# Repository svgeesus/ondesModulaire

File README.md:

ondesModulaire
==============

Eurorack analog synth implementation of ondes Martenot. This uses a
mixture of commercial and DIY modules. The controllers and the speakers
are all DIY. See [the patch](Patch.md).

This repository documents the DIY modules that I am making specific to
this project (as opposed to kits or designs made by others).

- [Precision rectifier](precision%20rectifier/readme.md)
- [Dual Comparator](dual%20comparator/)
- [ondesMix](wavemix/)
- [Offsets](offsets/)

It is also documenting the controllers I am making, and the speakers.

The keyboard controller was started, was partly working, and was then
abandoned as the keybed was too heavy for the keyboard shake vibrato function.
The keys were also regular sized rather than the smaller OM style.
Documentation at http://nantonos.github.io/ondesModulaire/keyboard/docs/

Lastly, this repository houses resources (screenshots, recordings, notes)
related to ongoing experiments to find the best emulation.

[Planned state of the modules](http://www.modulargrid.net/e/racks/view/30175) is available on Modular Grid and is updated
as experiments proceed.

The [actual current state](http://www.modulargrid.net/e/racks/view/61770) is also available and is updated as modules are purchased, built, or designed and built,
respectively.

A [discussion thread on Muffs forum](http://www.muffwiggler.com/forum/viewtopic.php?p=1261346) is the main place where this and related
projects are discussed

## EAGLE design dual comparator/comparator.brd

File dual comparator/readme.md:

# Dual Comparator

## Introduction

This 6HP dual module is a pair of simple comparator circuits, which turns triangle waves into a pulse waves with variable mark/space ratio. It takes two audio inputs and two control voltages, compares them, and outputs the result. If a CV is not patched, a variable voltage is used (derived from a voltage reference and a pot).

If the input waveform is a triangle wave, the output is a pulse wave with a variable mark-space ratio controlled by the CV.

I needed this because the Ondes Martenot has _two_ pulse waveforms: Gambe and Nasillard.
Gambe is roughly a pulse wave with 45% mark/space. (Petit gambe is a lowpass-filtered version of Gambe).
Nasillard is another pulse, but with around 5% mark/space.

## Features

- two audio ins (in2 normalized to in1)
- two PW cv ins (normalized to 5V)
- two pulse outputs
- two pots, for attenuverters

## Implementation

Choice of op-amp to use as comparator informed by [AN-849 Using Op Amps as Comparators](./AN-849.pdf) and in particular, transition time, overload recovery time and absence of phase reversal. A small amount of positive feedback provides some hysteresis to give clean switching even if the input signal has noise around the switching threshold.

- two trimmers, to null attenuverter
- low cost REF195 5V ref (direct to norm pots)
- two audio input buffers (2 audio) TL074
- two CV attenuverters (other half of 074)
- LT1213 dual op-amp as comparator
- 10k/15k resistive divider converts +/- 12V output to+/- 5V output. Volt swing and slew rate of comparator is reduced by current draw.
- two output buffers (TL072) with 47R output impedance.
- small pcb with just 2 pots. 6 jacks wired to pcb.

[Schematic (PDF)](schematic.pdf)

 ([PDF](board.pdf))

]

[Bill of Materials](dual_comparator_BOM.md)

Front panel [FPD](./dual_comparator.fpd)

## Special Bonus Feature

This module was designed to sit next to an Intellijel Dixie 2 oscillator, providing an additional two pulse waveforms. The Dixie 2 has coarse and fine tune pots, and also on the PCB a three-pin connector for an optional, third, ultrafine tune. There was spare space on this module so I added a handy ultra-fine-tune pot. There are no jacks for this, use a 3-pin jumper cable to go from the internal 3-pin connector
to the 3-pin ultrafine connector on the Dixie.

This is utterly unrelated to the comparator functionality.

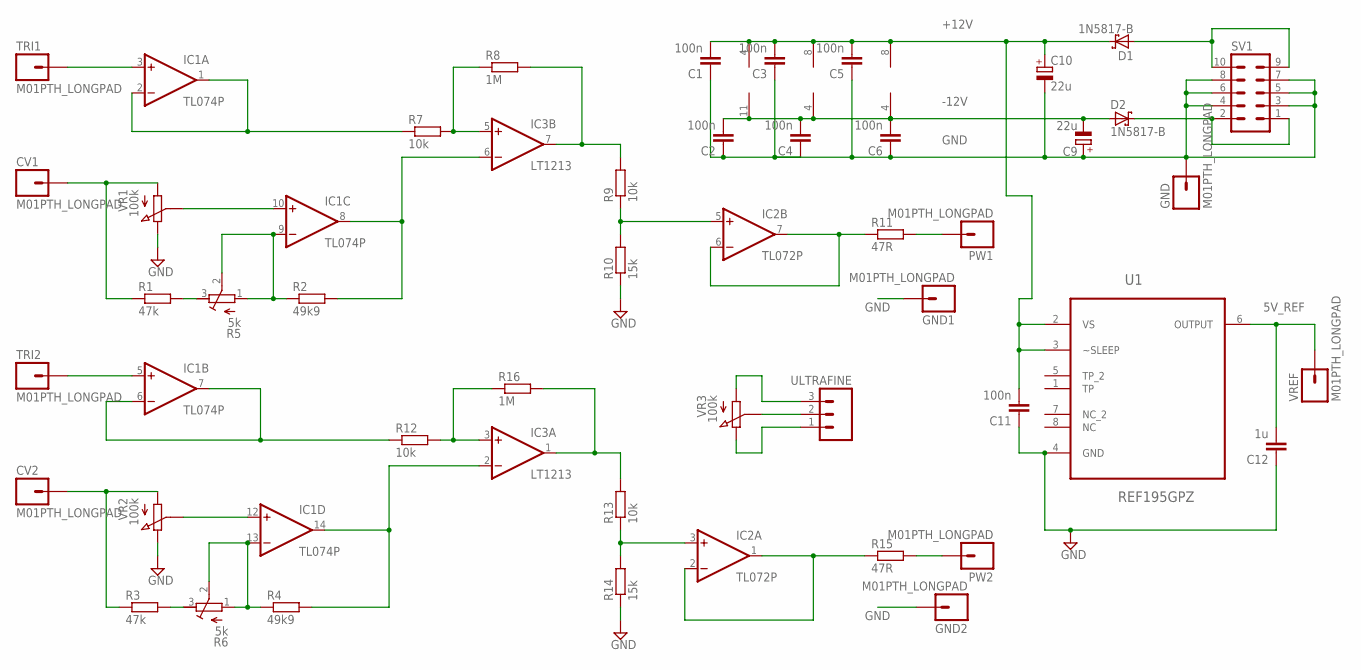
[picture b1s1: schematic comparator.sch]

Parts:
C1, C2, C3, C4, C5, C6, C11: 100n; C025-025X050
C9, C10: 22u; E2,5-5
C12: 1u; C050-025X075
CV1, CV2: M01PTH_LONGPAD; 1X01_LONGPAD
D1, D2: 1N5817-B; DO41-7.6
GND, GND1, GND2: M01PTH_LONGPAD; 1X01_LONGPAD
IC1: TL074P; DIL14
IC2: TL072P; DIL08
IC3: LT1213; DIL08
PW1, PW2: M01PTH_LONGPAD; 1X01_LONGPAD
R1, R3: 47k; 02.5-06.8/10
R2, R4: 49k9; 02.5-06.8/10
R5, R6: 5k; RTRIM3296W
R7, R9, R12, R13: 10k; 02.5-06.8/10
R8, R16: 1M; 02.5-06.8/10
R10, R14: 15k; 02.5-06.8/10
R11, R15: 47R; 02.5-06.8/10
SV1: MA05-2
TRI1, TRI2: M01PTH_LONGPAD; 1X01_LONGPAD
U1: REF195GPZ; DIP254P762X533-8
ULTRAFINE: M03LOCK; 1X03_LOCK
VR1, VR2, VR3: 100k; BI_9MM_SIDE
VREF: M01PTH_LONGPAD; 1X01_LONGPAD

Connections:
5V_REF: C12.2, U1.6 (OUTPUT), VREF.1
+12V: C1.2, C3.2, C5.2, C10.+, C11.2, D1.C, IC1.4 (V+), IC2.8 (V+), IC3.8 (V+), U1.2 (VS), U1.3 (~SLEEP)
-12V: C2.2, C4.2, C6.2, C9.-, D2.A, IC1.11 (V-), IC2.4 (V-), IC3.4 (V-)
GND: C1.1, C2.1, C3.1, C4.1, C5.1, C6.1, C9.+, C10.-, C11.1, C12.1, GND.1, GND1.1, GND2.1, R10.P$1 (1), R14.P$1 (1), SV1.3, SV1.4, SV1.5, SV1.6, SV1.7, SV1.8, U1.4 (GND), VR1.TOP, VR2.TOP
unnamed: IC1.3 (+IN), TRI1.1
unnamed: IC1.1 (OUT), IC1.2 (-IN), R7.P$1 (1)
unnamed: IC3.5 (+IN), R7.P$2 (2), R8.P$1 (1)
unnamed: PW1.1, R11.P$2 (2)
unnamed: IC1.10 (+IN), VR1.WIPER
unnamed: R3.P$2 (2), R6.3 (A)
unnamed: R1.P$2 (2), R5.3 (A)
unnamed: IC1.9 (-IN), R2.P$1 (1), R5.1 (E), R5.2 (S)
unnamed: IC1.8 (OUT), IC3.6 (-IN), R2.P$2 (2)
unnamed: IC3.7 (OUT), R8.P$2 (2), R9.P$2 (2)
unnamed: IC2.5 (+IN), R9.P$1 (1), R10.P$2 (2)
unnamed: IC2.6 (-IN), IC2.7 (OUT), R11.P$1 (1)
unnamed: IC3.3 (+IN), R12.P$2 (2), R16.P$1 (1)
unnamed: IC1.5 (+IN), TRI2.1
unnamed: IC1.6 (-IN), IC1.7 (OUT), R12.P$1 (1)
unnamed: IC1.12 (+IN), VR2.WIPER
unnamed: IC1.13 (-IN), R4.P$1 (1), R6.1 (E), R6.2 (S)
unnamed: IC1.14 (OUT), IC3.2 (-IN), R4.P$2 (2)
unnamed: IC3.1 (OUT), R13.P$2 (2), R16.P$2 (2)
unnamed: IC2.3 (+IN), R13.P$1 (1), R14.P$2 (2)
unnamed: IC2.1 (OUT), IC2.2 (-IN), R15.P$1 (1)
unnamed: PW2.1, R15.P$2 (2)
unnamed: ULTRAFINE.3, VR3.BOTTOM
unnamed: ULTRAFINE.1, VR3.TOP
unnamed: D1.A, SV1.9, SV1.10
unnamed: ULTRAFINE.2, VR3.WIPER
unnamed: D2.C, SV1.1, SV1.2
PW_CV1: CV1.1, R1.P$1 (1), VR1.BOTTOM
PW_CV2: CV2.1, R3.P$1 (1), VR2.BOTTOM

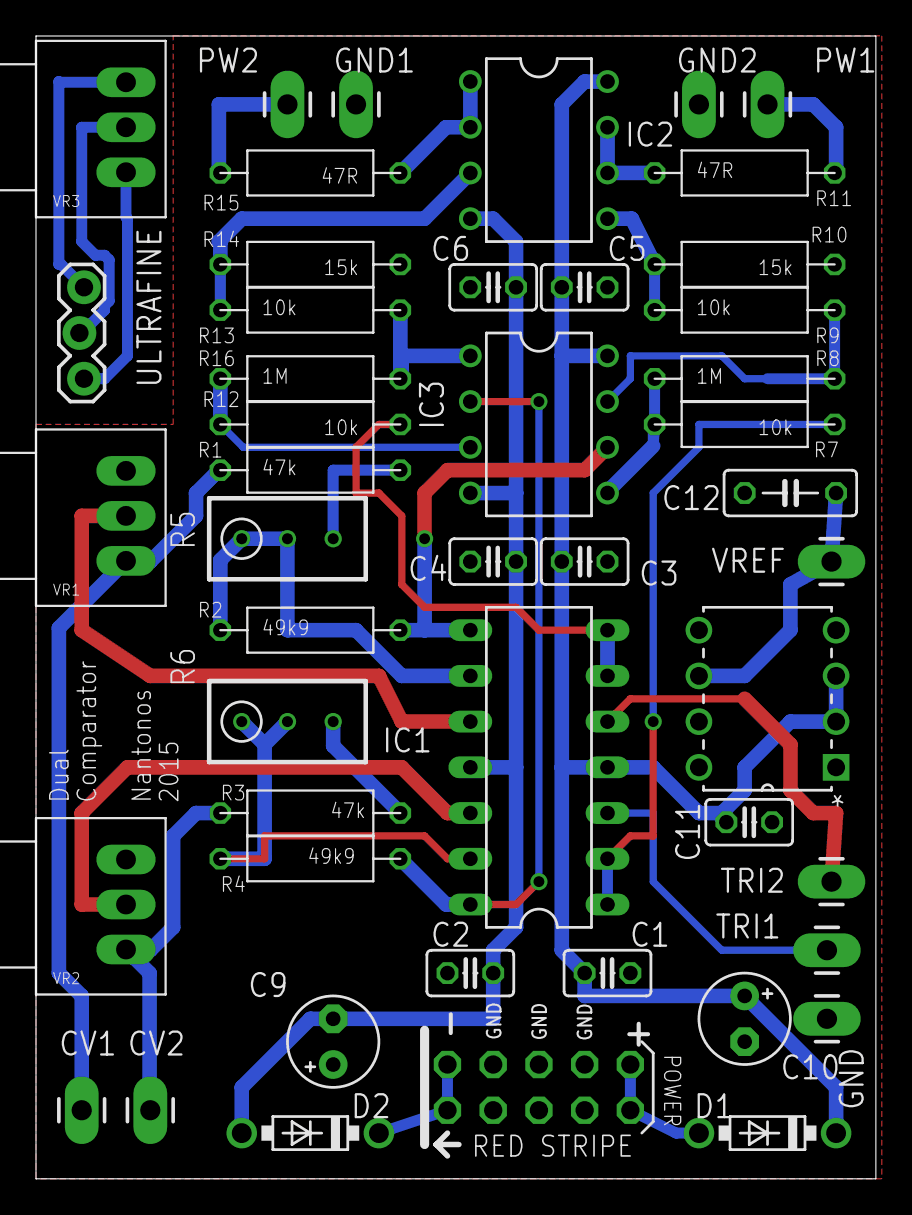
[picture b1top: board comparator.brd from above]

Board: 2 copper layers, 46.7 x 63.5 mm, 47 parts (0 on the bottom side), 33 nets.

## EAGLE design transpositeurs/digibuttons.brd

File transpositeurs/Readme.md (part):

# Digital implementation of transpositeurs (pitch shift buttons)

Transpositeurs are a set of six buttons,
in the tiroir of an ondes Martenot,
placed to the right of the _touche d'intensité_,
which produce small shifts in pitch.
They may be pressed in combination to generate larger shifts.
Effectively, a quantized pitchbend.

|  button   |   tones  |  semitones   | millivolts (semitones /12)    | interval     |
|--:        |--:       |--:           |--:                            |--:           |
| 1         | -1/4     | -0.5         |   -41.6666666666666667        | quarter-down |
| 2         | +1/4     | +0.5         |    41.6666666666666667        | quarter-up   |
| 3         | +1/2     | +1           |    83.3333333333333333        | semitone     |
| 4         | +1       | +2           |  166.666666666666667          | tone         |
| 5         | +2       | +4           |  333.333333333333333          | third        |
| 6         | +3 1/2   | +7           |  583.333333333333333          | fifth        |
| 2to6      |          | 14.5         | 1208.33333333333              |              |

Total swing 1,208.33333333333 - -41.6666666666667 = 1.250000V

My initial design attempts were purely analog. However,
analog buttons circuit is basically a DAC, so try designing as a DAC.

Since this is MCU based
and it only adds a couple of resistors and a connector,
an optional MIDI out is provided.

## Component selection

### MCU

A Teensy LC is ample for this simple circuit.

Make as an SPI board with 5V input (for vref, needs 1mA) and Euro ±12V (for op-amps).
Power DAC with 3V3 from Teensy? Or add on-board regulator for 3V3?
DAC needs 270(typ) 550(max) μA so power from Teensy 3V3 seems totally fine.

Teensy SPI for DAC on 10 (cs), 11 (Dout MOSI) 13 (SCLK)
free pins - maybe LEDs for buttons?

buttons not matrixed, hardware debounce, trigger interrupts.
transp. buttons need 6 inputs: 4,5,6,7,8,9

* try with bounce lib rather than hardware debounce.

breadboard debounce circuit, test debounced switch to interrupt ISR.
breadboard analog post-DAC circuit using Teensy LC pin14 DAC just for testing.

Could also have MIDI out on pin 1 TX1. Just send pitchbend.

### DAC

Total swing = 29 demi-semitones. Use DAC with total swing of n*32 so each
demisemitone is n integral steps, and avoid dac codes at the ends to
eliminate zero offset and max offset errors.

Aim is better than 1 cent accuracy = 1/50n so if n > 2^6 = 1/64n, for 1 lsb INL

Thus only needs a 12bit DAC (with very good <1.0 INL and DNL, n = 2^7 = 128) or
14bit with <4 INL, DNL, n = 2^9 = 512
16bit with <16INL, DNL

**LTC1658CS8** 14bit SPI SOIC-8 [got, ordered 13 Sep 2014]
SOIC-8, 3V3 or 5V operation
DNL ±1.0 LSB max, DNL graph shows ±0.2 LSB typ
INL ±8.0 LSB max (more than 0.1V from rails), but INL graph shows typ +1, -2LSB
DNL, INL assume Vref < Vcc -0.1V so use 3V ref and 3V3 rail.
zero error 4mV over temperature -40 to +85°C = DAC count 21.8 so avoid counts 0 to 22
offset error ±4.0 mV max over temperature -40 to +85°C so avoid counts 16,361 to 16,383
Offset Error Temperature Coefficient ±5 μV/°C
Gain error ±20 LSB
Gain Error Drift ±2.5 ppm/°C
Vref input resistance 30k min, so current = 100μA.
$6.05 from Linear, singly, min order 2; have both MSOP and DIP8
$10.27 from Mouser, moq 1

1LSB = 3 ÷ 2^14 = 183μV at DAC out, 1 cent is 833μV so 4.5LSB per cent.
but less than this as the DAC output is scaled down to total swing.

### Vref

DAC needs external vref, preferably a bit lower than Vcc so 3.0V would be good.
AD780 or, better and cheaper, MAX6126-3

**AD780BNZ**  1mv initial accuracy 3ppm/°C PDIP [got]
needs 1μF from VCC to GND
[ to lower noise, add 100nF from pin3 to GND and 100μF from 3V ref output to GND
(fig.9 in datasheet)
normal noise is 1.2ppm = 3.6μV so not worth it ]

**LT6658AIDE-3** 0.5mV initial accuracy 10ppm/°C  SOIC-8
Temp drift essentially flat from 20 to 40°C (fig.11)

**MAX6126A30+** 0.6mV (0.02%) A grade initial accuracy, 3ppm/°C SOIC-8
0.1μF to 10μF (best: 10μF // 0.1μF) output cap close to DAC Ref input.
0.1μF input cap and optional 0.1μF noise cap.

### Op-amps

Op-amps, use a quad SOIC-14.

**OPA4172ID** ±200μV (typ) ±1mV (max @ 25°C) ±1.15mV (max over 40°C to +125°C) offset. 240millicent (typ) 1.3cent (max over temp). **$2.84/10**

**OPA4197ID**  ±25μV (typ) ±100μV (max @ 25°C)  120millicent (max @ 25°C ) **$3.39/10** (IDR version)

### Resistors

### Misc

DAC needs 1μF from Vcc to GND. Op amps need usual 100n from +12V and -12V to GND.

## Full scale swing

Most negative value (1 pressed) -0.5/12 = -41.6666666666666667
Most positive value (2,3,4,5,6 all pressed)
583.333333333333333 + 333.333333333333333 + 166.666666666666667 + 83.3333333333333333 + 41.6666666666666667
= 1,208.33333333333333

Total swing 1,208.33333333333 + 41.6666666666667 = 1.250V.

Make DAC with around convenient unipolar swing, trim offset
to get negative 0.5semi lowest (ie trim for zero volts when sending code
for no buttons pressed), trim gain to get exact value when
highest shift (buttons 2-6 all pressed).

### Values at all button combinations

Values in demi-semitones (multiples of 50 cents) where n=512 for 14-bit DAC.

Code to voltage is 3V / (2^14-1) = **183.116645303058mV**

Voltages at code 0 and code 2^14-1 are approximate, due to zero and fs error terms.
_Do not measure_ at these code points.

DAC voltage then offset to generate 0V at _no buttons pressed_
(and thus, -41.6667 mV with button 1 pressed)

(DAC - offset) is then scaled, so output voltage for (button 2 to 6) is exactly 1208.33333333333mV

Values below are _before_ the DAC scaling, except for the last column.

| buttons       |  dstones       |  code  | (code * 512)  |  DAC output V      |  (V - offs)  | scaled (V-offs) |
|:--            |--:             |--:     |--:            |--:                 |--:           |--:              |
| unused        |                | 0      |            0  | 0V                 | ~-187.51mV   | around -83mV    |
| 1             | -1             | 1n     |          512  |  93.755722mV       | -93.755722mV | -41.6667mV      |
| none          |  0             | 2n     |         1024  | __187.51144mV__    | 0V           | 0V              |
| 2             |  1             | 3n     |         1536  |                    |              |                 |
| 3             |  2             | 4n     |               |                    |              |                 |
| 2+3, 4+1      |  3             | 5n     |               |                    |              |                 |
| 4             |  4             | 6n     |               |                    |              |                 |
| 4+2           |  5             | 7n     |               |                    |              |                 |
| 4+3           |  6             | 8n     |               |                    |              |                 |
| 5+1           |  7             | 9n     |               |                    |              |                 |
| 5             |  8             | 10n    |               |                    |              |                 |
| 5+2           |  9             | 11n    |               |                    |              |                 |
| 5+3           | 10             | 12n    |               |                    |              |                 |
| 5+3+2         | 11             | 13n    |               |                    |              |                 |
| 5+4           | 12             | 14n    |               |                    |              |                 |
| 5+4+2, 6+1    | 13             | 15n    |               |                    |              |                 |
| 6, 5+4+3      | 14             | 16n    |               |                    |              |                 |
| 6+2, 5+4+3+2  | 15             | 17n    |               |                    |              |                 |
| 6+3           | 16             | 18n    |               |                    |              |                 |
| 6+3+2         | 17             | 19n    |               |                    |              |                 |
| 6+4           | 18             | 20n    |               |                    |              |                 |
| 6+4+2         | 19             | 21n    |               |                    |              |                 |
| 6+4+3         | 20             | 22n    |               |                    |              |                 |
| 6+5+1         | 21             | 23n    |               |                    |              |                 |
| 6+5           | 22             | 24n    |               |                    |              |                 |
| 6+5+2         | 23             | 25n    |               |                    |              |                 |
| 6+5+3         | 24             | 26n    |               |                    |              |                 |
| 6+5+4+1       | 25             | 27n    |               |                    |              |                 |
| 6+5+4         | 26             | 28n    |               |                    |              |                 |
| 6+5+4+3+1     | 27             | 29n    |               |                    |              |                 |
| 6+5+4+3       | 28             | 30n    |               |                    |              |                 |
| 6+5+4+3+2     | 29             | 31n    |        15872  |  2.90642V          |  2.7189159V  |   1.2083333V    |
| unused        | 30             | 32n-1  |        16383  | ~3.000V            | ~2.81249V    |  ~1.250000V     |

### Dac scale factor

Unscaled DAC swing for nominal 3V FS is (V(31n) - V(1n)) = (2.90642739425014 - 0.09375572239517) = 2.81267167185497
Scale factor is

1.25 / 2.81267167185497 = __0.44441731770833__

So with an input resistor of 10k the feedback resistor is 4k444
closest E96 4k42 which is 24R low. So a 50R trimmer?

 1LSB = ( 3 × 0.444444444 ) / ( 2^14 ) = 8.13802082519531E-5
 = 81μV at op-amp out
 = 8.13802082519531E-5 * 1,200 = 97.65 millicents

tolerances:
Susumu RG2012V-103-P-T1 10k 0.02% 5ppm $2.60/25

* error on 10k is 2R
* error on 4k42 is 0.8R (!)

MAX6126-3 has initial accuracy ±0.5mV

31n expected value from table above is 2.90642V before mixing in the offset.
3.000 × 15872 / 16383 × 4444/10000
= 1.29161633400476

worst case high (Vref high, resistor tolerances tip to high, gain error +20LSB so 15872 is like 15892)
31n is 3.0005 × (15892 / 16383) × (4420.8 + 24 / 9998)
= 3.0005 × (15,892 / 16,383) × ((4,420.8 + 24) / 9,998)
= 1.29395105158369
2.335mV high

worst case low (Vref low, resistors to low, gain error -20LSB so 15872 is like 15852)
31n is 2.9995 × (15852/16,383) × ((4,419.2 + 24) / 10002)
= 1.28928375587655
-2.333mV low

same but now setting 50R trimmer to 0, to compensate
3.0005 × (15,892 / 16,383) × ((4,420.8) / 9,998)
= 1.28696427484728
= 4.652mv low, so easily covers the required adjustment

same but now setting 50R trimmer to 50, to compensate
2.9995 × (15852/16,383) × ((4,419.2 + 50) / 10002)
= 1.2968281782867
= 5.212mV high

### Negative voltage offset

Offset is 3 × 1,024 / 16,383 = 0.18751144479033
Before scaling, 187.511mV to take 'none' to 0V

With 3V ref, voltage divider 10 / 0.18751144479033 * 3 = 159.990234375 so 150k to 10k
E96 values 150k
BUT
After DAC scaling, 2n is 3.000 × 1024 / 16383 × 4444/10000
= 83.330mV
divider is 35k700 to 1020

tolerances:
Susumu RG2012V-103-P-T1 10k 0.02% 5ppm $2.60/25 error on 1k020 is 0.2R
and (for values > 10k) Susumu RG2012N-104-W-T1 100k 0.05%  10ppm $0.753/25 error on 35k700 is 18R
MAX6126-3 has initial accuracy ±0.5mV

worst case high: 3.0005 × 1020.2 / (35682 + 1020.2)
= 83.404mV 70μV high (85 millicents)

worst case low: 2.9995 × 1019.8 / ( 35718 + 1019.8)
= 83.263mV 70μV low (85 millicents)

These tiny errors do not merit a trimmer;
the increased tempco of the trimmer plus end stop resistance variability outweighs any advantage.

However, these E96 values are not readily available at those tolerances
so redo calculations with 0.1%:

Error on 1k020 is 1.02R; error on 35k700 is 35.7R (!!)

worst case high: 3.0005 × 1021 /(35664 + 1021)
= 0.08350853209759
= 178μV high (214 millicents)

worst case low: 2.9995 × 1019 / (35736 + 1019)
= 0.0831584954428
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
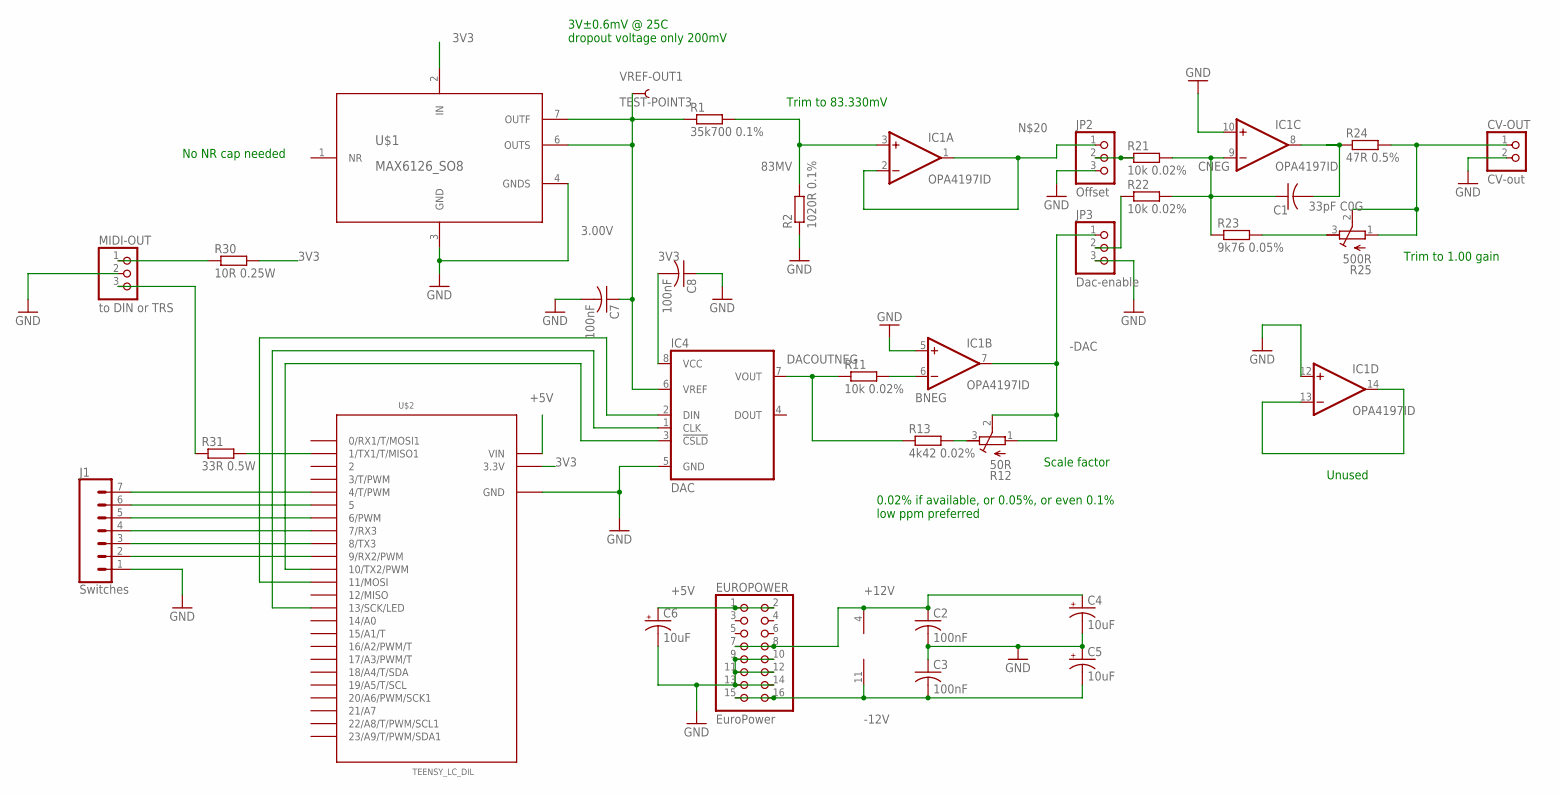
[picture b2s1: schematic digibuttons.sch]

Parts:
C1: 33pF C0G; C0805
C2, C3, C7, C8: 100nF; C1206
C4, C5, C6: 10uF; CPOL-RADIAL-2.5MM-5MM
CV-OUT: CV-out; 1X02
EUROPOWER: EuroPower; 2X08
IC1: OPA4197ID; SO14
IC4: DAC; SOIC8_208MIL
J1: Switches; 1X07_LOCK
JP2: Offset; 1X03
JP3: Dac-enable; 1X03
MIDI-OUT: to DIN or TRS; 1X03
R1: 35k700 0.1%; R0805
R2: 1020R 0.1%; R0805
R11, R21, R22: 10k 0.02%; R0805
R12: 50R; RTRIM3296W
R13: 4k42 0.02%; R0805
R23: 9k76 0.05%; R0805
R24: 47R 0.5%; R0805
R25: 500R; RTRIM3296W
R30: 10R 0.25W; 10MM_RESISTOR
R31: 33R 0.5W; 10MM_RESISTOR
U$1: MAX6126_SO8; SO08
U$2: TEENSY_LC_DIL; TEENSY_3.0-3.2&LC_DIL
VREF-OUT1: TEST-POINT3; PAD.03X.03

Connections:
3.00V: C7.1, IC4.6 (VREF), R1.1, U$1.6 (OUTS), U$1.7 (OUTF), VREF-OUT1.P$1
3V3: C8.2, IC4.8 (VCC), R30.2, U$1.2 (IN), U$2.3.3V
83MV: IC1.3 (+IN), R1.2, R2.2
+5V: C6.1 (+), EUROPOWER.1, EUROPOWER.2, U$2.VIN
+12V: C2.1, C4.1 (+), EUROPOWER.7, EUROPOWER.8, IC1.4 (V+)
-12V: C3.2, C5.2 (-), EUROPOWER.15, EUROPOWER.16, IC1.11 (V-)
-DAC: IC1.7 (OUT), JP3.1, R12.1 (E), R12.2 (S)
BNEG: IC1.6 (-IN), R11.2
CNEG: C1.1, IC1.9 (-IN), R21.2, R22.2, R23.1
CS: IC4.3 (!CSLD), U$2.10 (10/TX2/PWM)
DACOUTNEG: IC4.7 (VOUT), R11.1, R13.1
GND: C2.2, C3.1, C4.2 (-), C5.1 (+), C6.2 (-), C7.2, C8.1, CV-OUT.2, EUROPOWER.9, EUROPOWER.10, EUROPOWER.11, EUROPOWER.12, EUROPOWER.13, EUROPOWER.14, IC1.5 (+IN), IC1.10 (+IN), IC1.12 (+IN), IC4.5 (GND), J1.1, JP2.3, JP3.3, MIDI-OUT.2, R2.1, U$1.3 (GND), U$1.4 (GNDS), U$2.AGND (GND), U$2.GND
MOSI: IC4.2 (DIN), U$2.11 (11/MOSI)
unnamed: MIDI-OUT.1, R30.1
unnamed: R31.2, U$2.1 (1/TX1/T/MISO1)
unnamed: IC1.13 (-IN), IC1.14 (OUT)
unnamed: JP3.2, R22.1
unnamed: MIDI-OUT.3, R31.1
unnamed: JP2.2, R21.1
unnamed: R23.2, R25.3 (A)
unnamed: C1.2, IC1.8 (OUT), R24.1
unnamed: CV-OUT.1, R24.2, R25.1 (E), R25.2 (S)
unnamed: J1.2, U$2.9 (9/RX2/PWM)
unnamed: R12.3 (A), R13.2
unnamed: J1.3, U$2.8 (8/TX3)
unnamed: J1.4, U$2.7 (7/RX3)
unnamed: J1.5, U$2.6 (6/PWM)
unnamed: J1.6, U$2.5
unnamed: J1.7, U$2.4 (4/T/PWM)
unnamed: IC1.1 (OUT), IC1.2 (-IN), JP2.1
SCLK: IC4.1 (CLK), U$2.13 (13/SCK/LED)

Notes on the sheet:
3V±0.6mV @ 25C dropout voltage only 200mV
Unused
No NR cap needed
Trim to 1.00 gain
Scale factor
Trim to 83.330mV
0.02% if available, or 0.05%, or even 0.1% low ppm preferred

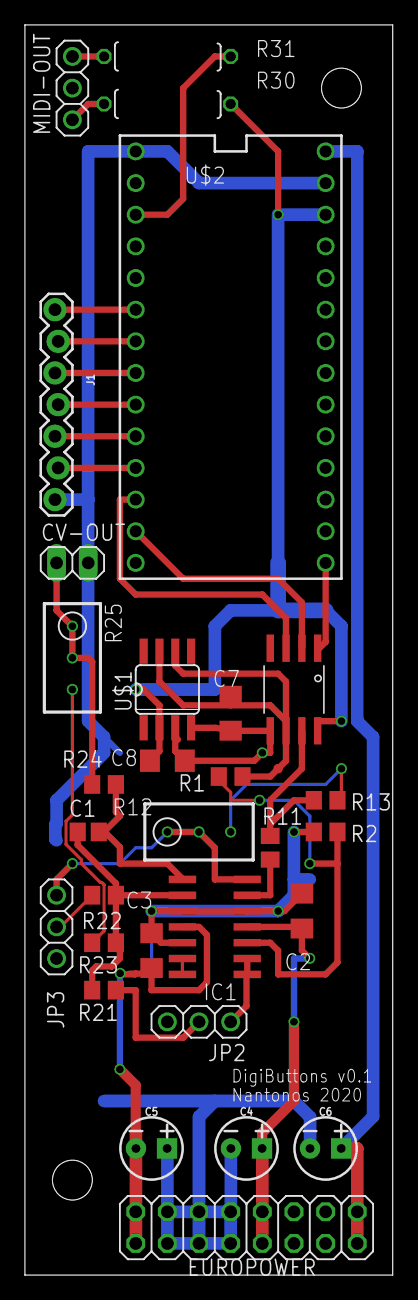
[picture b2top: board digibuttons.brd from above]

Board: 2 copper layers, 29.5 x 100.3 mm, 33 parts (0 on the bottom side), 31 nets.

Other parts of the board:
U$3, U$4: MOUNTING_HOLE

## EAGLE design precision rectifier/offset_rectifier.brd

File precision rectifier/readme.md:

# Octaviant wavefolder

This module is to produce the Ondes Martenot "Octaviant" waveform.

## First attempt - μFold

I was originally using the [Intellijel μFold II](http://www.modulargrid.net/e/intellijel-%CE%BCfold-ii) for this purpose

However, while this is a great module in general, for this specific
application it was not a good fit. The settings needed (2 folds,
almost minimal amount, some offset) were near one end of the module
range, and the resulting waveforms were smooth topped rather than sharply
folded as with the original.

In a real Ondes Martenot, this waveform is made with a bridge rectifier.
Because of the high voltages used, diode drops have little effect in the original circuit, while they would havea detrimental effect at Eurorack voltage levels.
Thus it seemed that a "precision rectifier" (which uses diodes in the
feedback loop of an op-amp, to eliminate the effect of diode drops) would
be a suitable replacement.

## Precision rectifier design

The rectifier circuit used here is not original and is straight from a
Burr-Brown application note ["PRECISION ABSOLUTE VALUE CIRCUITS"](http://www.ti.com/lit/an/sboa068/sboa068.pdf) by
David Jones and Mark Stitt, figure 1.

Following their table of op-amp choices, a fast OPA2134PA is used so that the
output circuit is glitch-free up to 20kHz. Because Jones & Stitt recommend
closely matched resistors in the precision rectifier, 0.1% metal film is
used at those locations.

The remainder of the circuit is a Eurorack power connector, a low-cost 5V
voltage reference for the offset, and an inverting op-amp to give -5V. A
front-panel potentiometer thus gives a continuously variable +5V to -5V offset.
TL072 is used as there are no particular requirements on the op-amps here
besides good buffering (so, FET input).

The value from the pot is normaled to the offset CV input jack socket, so with
no cable connected the pot value is used.

The input audio signal is buffered with an inverting op-amp then added to
the offset with an inverting summer (thus restoring the phase).

## Schematic & Layout

- [schematic (pdf)](offset_rectifier.pdf)
- [Eagle schematic](offset_rectifier.sch)
- [Eagle board](offset_rectifier.brd)
- [Bill of Materials](BOM.md)

The board was made at OSH Park.

Completed module:

Scope output, showing sharply-folded sine like the original Ondes Martenot waveform.

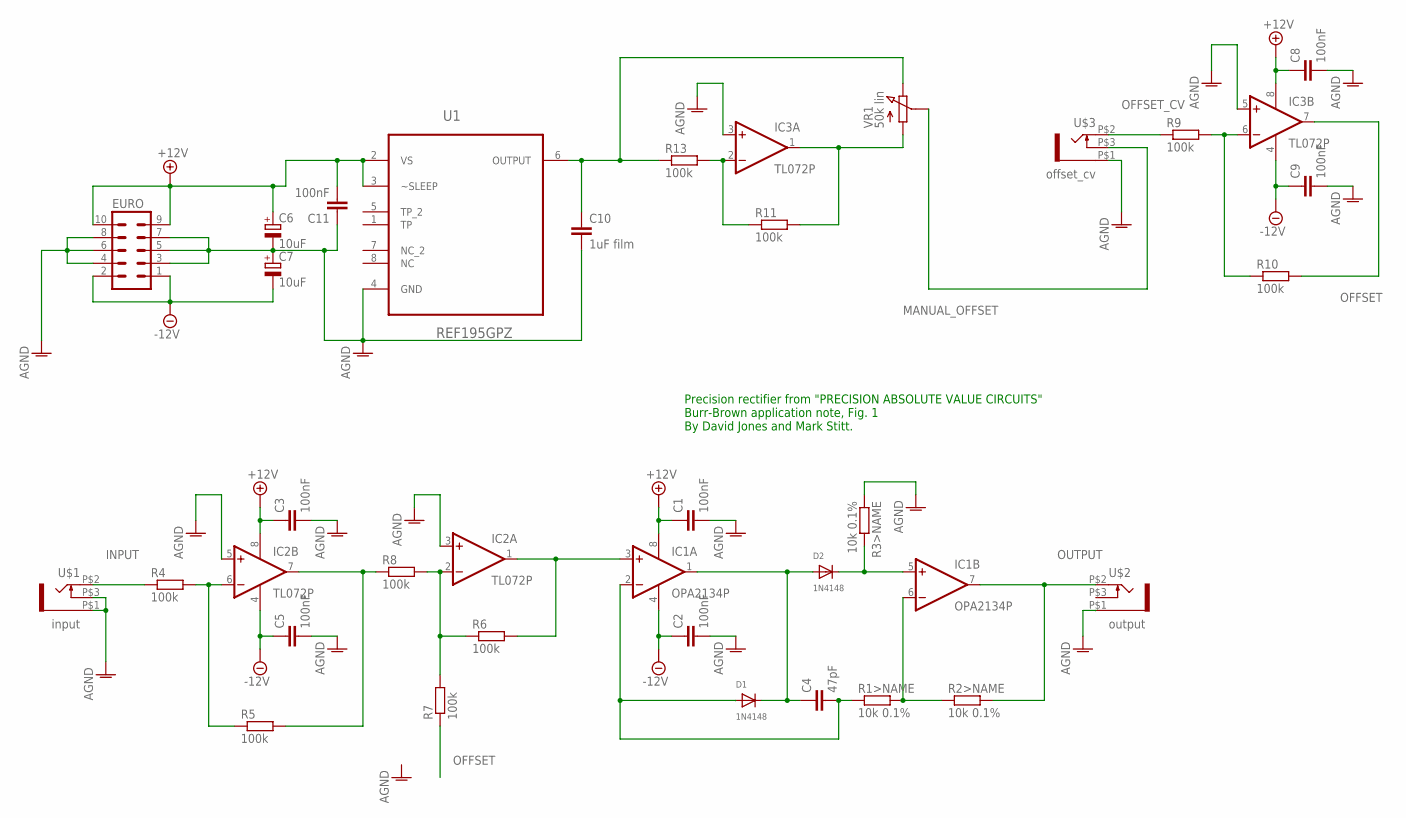
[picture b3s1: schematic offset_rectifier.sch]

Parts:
C1, C2, C3, C5, C8, C9, C11: 100nF; C2.5-3
C4: 47pF; C2.5-3
C6, C7: 10uF; E2,5-6E
C10: 1uF film; C050-025X075
D1, D2: 1N4148; DO-1N4148
EURO: MA05-2
IC1: OPA2134P; DIL08
IC2, IC3: TL072P; DIL08
R1, R2, R3: 10k 0.1%; 0409/12.5
R4, R5, R6, R7, R8, R9, R10, R11, R13: 100k; 02.5-06.8/10
U1: REF195GPZ; DIP254P762X533-8
U$1: input; PJ302M
U$2: output; PJ302M
U$3: offset_cv; PJ302M
VR1: 50k lin; BI_9MM_SIDE

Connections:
+12V: C1.1, C3.1, C6.+, C8.1, C11.2, EURO.9, EURO.10, IC1.8 (V+), IC2.8 (V+), IC3.8 (V+), U1.2 (VS), U1.3 (~SLEEP)
-12V: C2.1, C5.1, C7.-, C9.1, EURO.1, EURO.2, IC1.4 (V-), IC2.4 (V-), IC3.4 (V-)
AGND: C1.2, C2.2, C3.2, C5.2, C6.-, C7.+, C8.2, C9.2, C10.2, C11.1, EURO.3, EURO.4, EURO.5, EURO.6, EURO.7, EURO.8, IC2.3 (+IN), IC2.5 (+IN), IC3.3 (+IN), IC3.5 (+IN), R3.R$1 (1), U1.4 (GND), U$1.P$1 (RING), U$1.P$3 (SWITCH), U$2.P$1 (RING), U$3.P$1 (RING)
INPUT: R4.P$1 (1), U$1.P$2 (TIP)
MANUAL_OFFSET: U$3.P$3 (SWITCH), VR1.WIPER
unnamed: IC3.6 (-IN), R9.P$2 (2), R10.P$1 (1)
unnamed: C4.2, D1.A, IC1.2 (-IN), R1.R$1 (1)
unnamed: IC1.3 (+IN), IC2.1 (OUT), R6.P$2 (2)
unnamed: D2.C, IC1.5 (+IN), R3.P$2 (2)
unnamed: IC2.6 (-IN), R4.P$2 (2), R5.P$1 (1)
unnamed: IC1.6 (-IN), R1.P$2 (2), R2.R$1 (1)
unnamed: IC3.2 (-IN), R11.P$1 (1), R13.P$2 (2)
unnamed: C4.1, D1.C, D2.A, IC1.1 (OUT)
unnamed: IC3.1 (OUT), R11.P$2 (2), VR1.BOTTOM
unnamed: IC2.2 (-IN), R6.P$1 (1), R7.P$2 (2), R8.P$2 (2)
unnamed: IC2.7 (OUT), R5.P$2 (2), R8.P$1 (1)
unnamed: C10.1, R13.P$1 (1), U1.6 (OUTPUT), VR1.TOP
OFFSET: IC3.7 (OUT), R7.P$1 (1), R10.P$2 (2)
OFFSET_CV: R9.P$1 (1), U$3.P$2 (TIP)
OUTPUT: IC1.7 (OUT), R2.P$2 (2), U$2.P$2 (TIP)

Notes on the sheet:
Precision rectifier from "PRECISION ABSOLUTE VALUE CIRCUITS" Burr-Brown application note, Fig. 1 By David Jones and Mark Stitt.

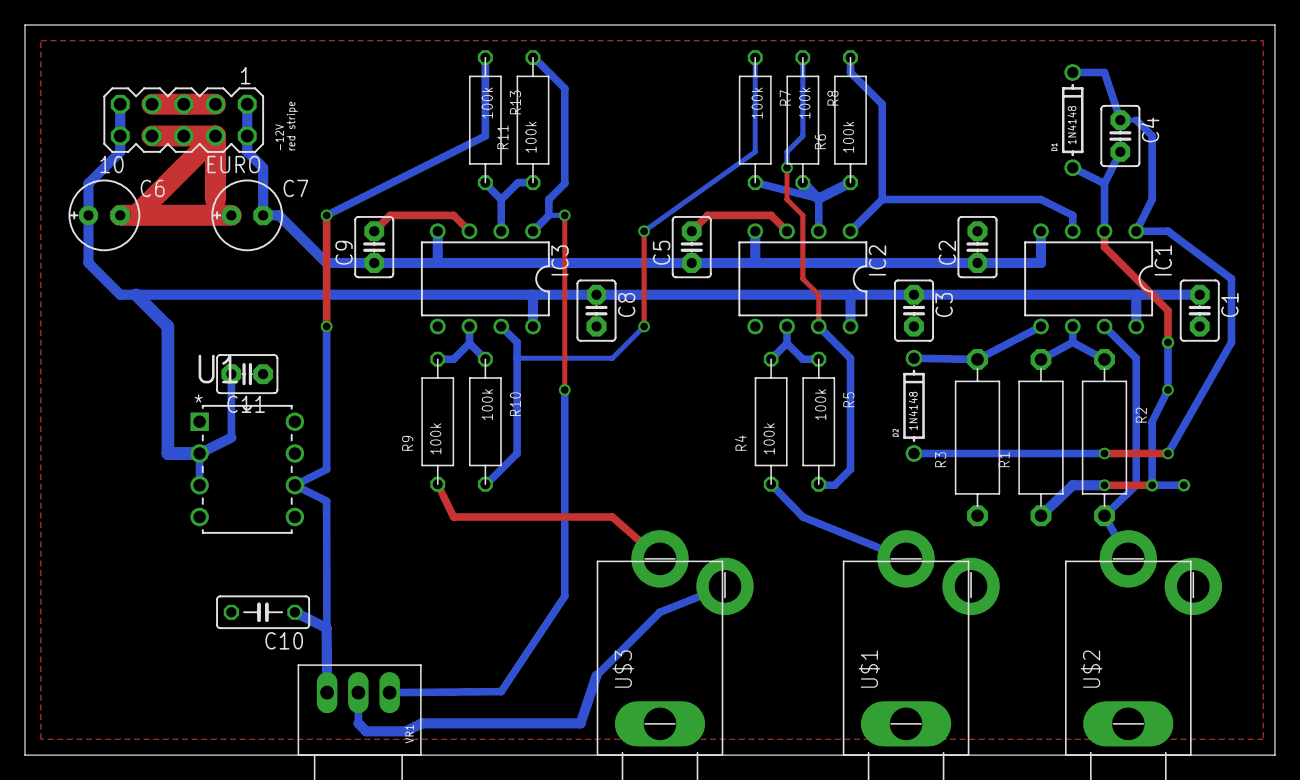
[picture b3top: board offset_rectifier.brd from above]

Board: 2 copper layers, 100.0 x 58.4 mm, 34 parts (0 on the bottom side), 20 nets.

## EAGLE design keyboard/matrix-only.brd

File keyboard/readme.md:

Teensy++ 2.0-based keyboard scanner for Fatar 49- and 61-key keyboards, with velocity. This is intended for an Ondes Martenot, using a 5 octave keyboard  and +/- 2 octave switching, giving 9 octaves in total. Output is pitch CV and gate, plus velocity (not needed for Ondes Martenot, but generally useful).

For flexibility, separate boards are used for the microcontroler and keyboard matrix, the pitch CV, velocity CV, and the ADC.

1 V/octave pitch CV in the range -2.5V to +7.5V is created with a highly linear, 16-bit SPI DAC (AD5542) and a precision 2.5V reference (AD780).  This generates bipolar +/- 2.5V via U4a. U4b inverts the 2.5V reference. U3b scales the DAC output by 2, giving +/- 5V. U3a is a summing inverter, used to offset the scaled DAC values to give -2.5 to +7.5V. The range -2V to +7V covers nine octaves, with 0V giving the same pitch as with Doepfer keyboards.

A second SPI DAC board, with dual 12bit DAC, will generate two more CVs in the range 0 to 5V. These could be note-on and note-off velocity, or keyboard shake, or other uses.

A 16bit I2C ADC is also planned, to read the Ondes Martenot 'bague'. This will output pitch CV using the same DAC as is used for the keyboard.

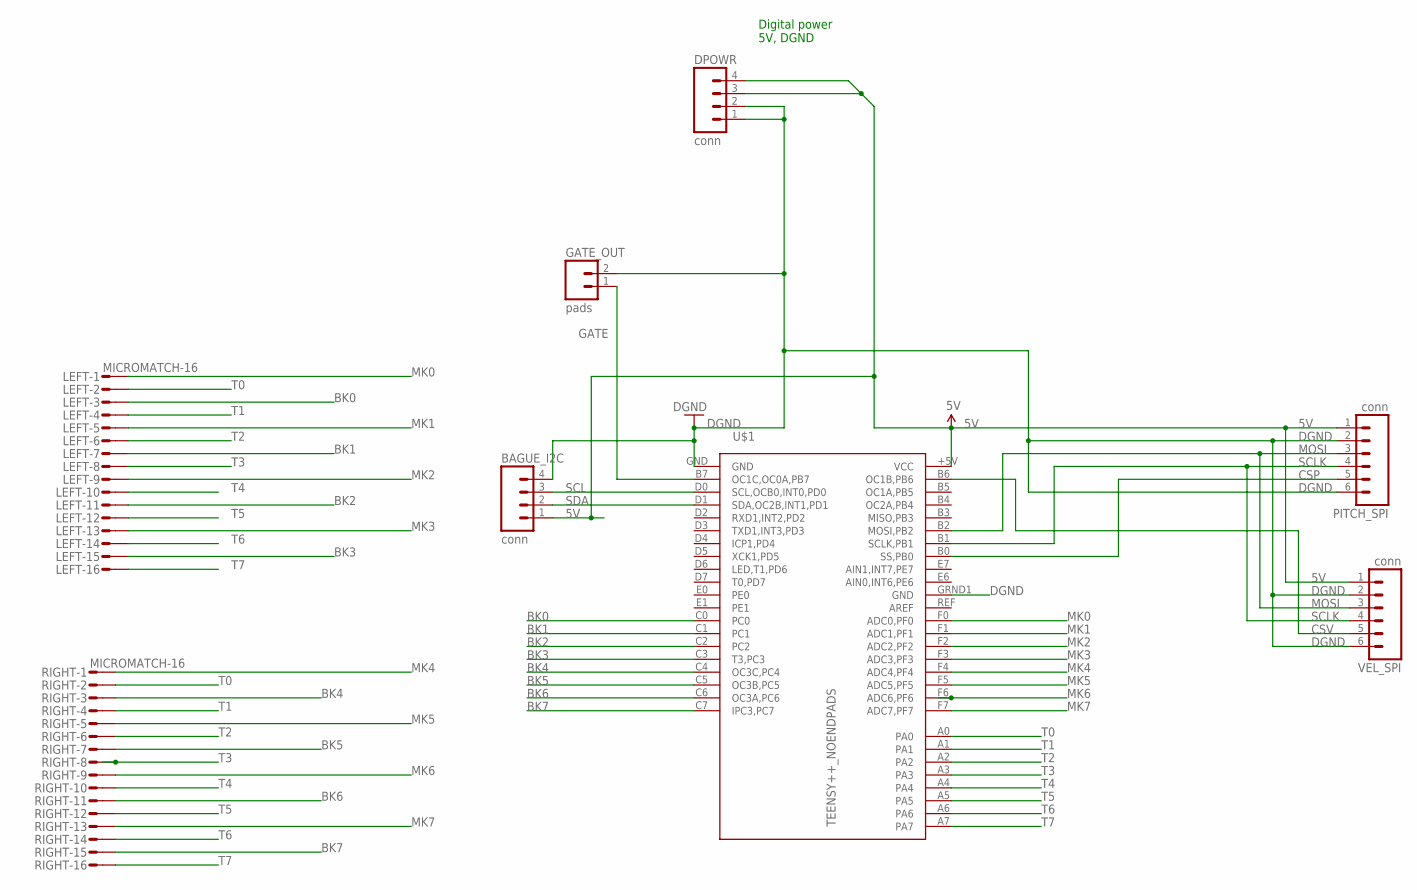
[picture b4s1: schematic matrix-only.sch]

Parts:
BAGUE_I2C: conn; 1X04_LOCK
DPOWR: conn; 1X04
GATE_OUT: pads; 1X02_LONGPADS
LEFT: MICROMATCH-16
PITCH_SPI: conn; 1X06
RIGHT: MICROMATCH-16
U$1: TEENSY++_NOENDPADS; TEENSY++
VEL_SPI: conn; 1X06

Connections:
5V: BAGUE_I2C.1, DPOWR.3, DPOWR.4, PITCH_SPI.1, U$1.+5V (VCC), VEL_SPI.1
BK0: LEFT.3, U$1.C0
BK1: LEFT.7, U$1.C1
BK2: LEFT.11, U$1.C2
BK3: LEFT.15, U$1.C3 (T3,PC3)
BK4: RIGHT.3, U$1.C4 (OC3C,PC4)
BK5: RIGHT.7, U$1.C5 (OC3B,PC5)
BK6: RIGHT.11, U$1.C6 (OC3A,PC6)
BK7: RIGHT.15, U$1.C7 (IPC3,PC7)
CSP: PITCH_SPI.5, U$1.B0 (SS,PB0)
CSV: U$1.B6 (OC1B,PB6), VEL_SPI.5
DGND: BAGUE_I2C.4, DPOWR.1, DPOWR.2, GATE_OUT.2, PITCH_SPI.2, PITCH_SPI.6, U$1.GND, U$1.GRND1 (GND), VEL_SPI.2, VEL_SPI.6
GATE: GATE_OUT.1, U$1.B7 (OC1C,OC0A,PB7)
MK0: LEFT.1, U$1.F0 (ADC0,PF0)
MK1: LEFT.5, U$1.F1 (ADC1,PF1)
MK2: LEFT.9, U$1.F2 (ADC2,PF2)
MK3: LEFT.13, U$1.F3 (ADC3,PF3)
MK4: RIGHT.1, U$1.F4 (ADC4,PF4)
MK5: RIGHT.5, U$1.F5 (ADC5,PF5)
MK6: RIGHT.9, U$1.F6 (ADC6,PF6)
MK7: RIGHT.13, U$1.F7 (ADC7,PF7)
MOSI: PITCH_SPI.3, U$1.B2 (MOSI,PB2), VEL_SPI.3
SCL: BAGUE_I2C.3, U$1.D0 (SCL,OCB0,INT0,PD0)
SCLK: PITCH_SPI.4, U$1.B1 (SCLK,PB1), VEL_SPI.4
SDA: BAGUE_I2C.2, U$1.D1 (SDA,OC2B,INT1,PD1)
T0: LEFT.2, RIGHT.2, U$1.A0
T1: LEFT.4, RIGHT.4, U$1.A1
T2: LEFT.6, RIGHT.6, U$1.A2
T3: LEFT.8, RIGHT.8, U$1.A3
T4: LEFT.10, RIGHT.10, U$1.A4
T5: LEFT.12, RIGHT.12, U$1.A5
T6: LEFT.14, RIGHT.14, U$1.A6
T7: LEFT.16, RIGHT.16, U$1.A7

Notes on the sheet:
Digital power 5V, DGND

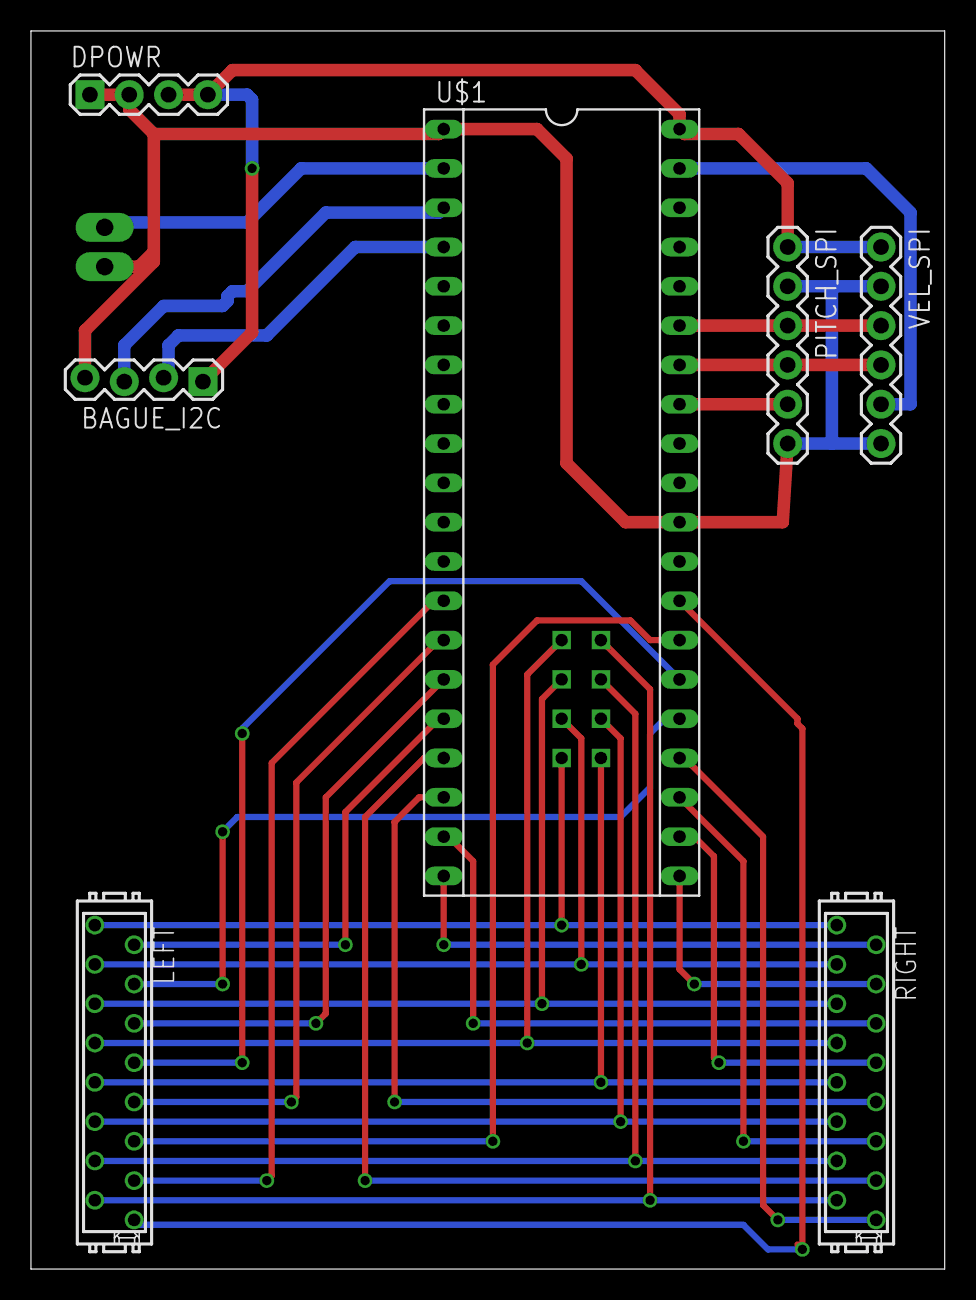
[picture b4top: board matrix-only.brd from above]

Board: 2 copper layers, 59.0 x 80.0 mm, 8 parts (0 on the bottom side), 33 nets.

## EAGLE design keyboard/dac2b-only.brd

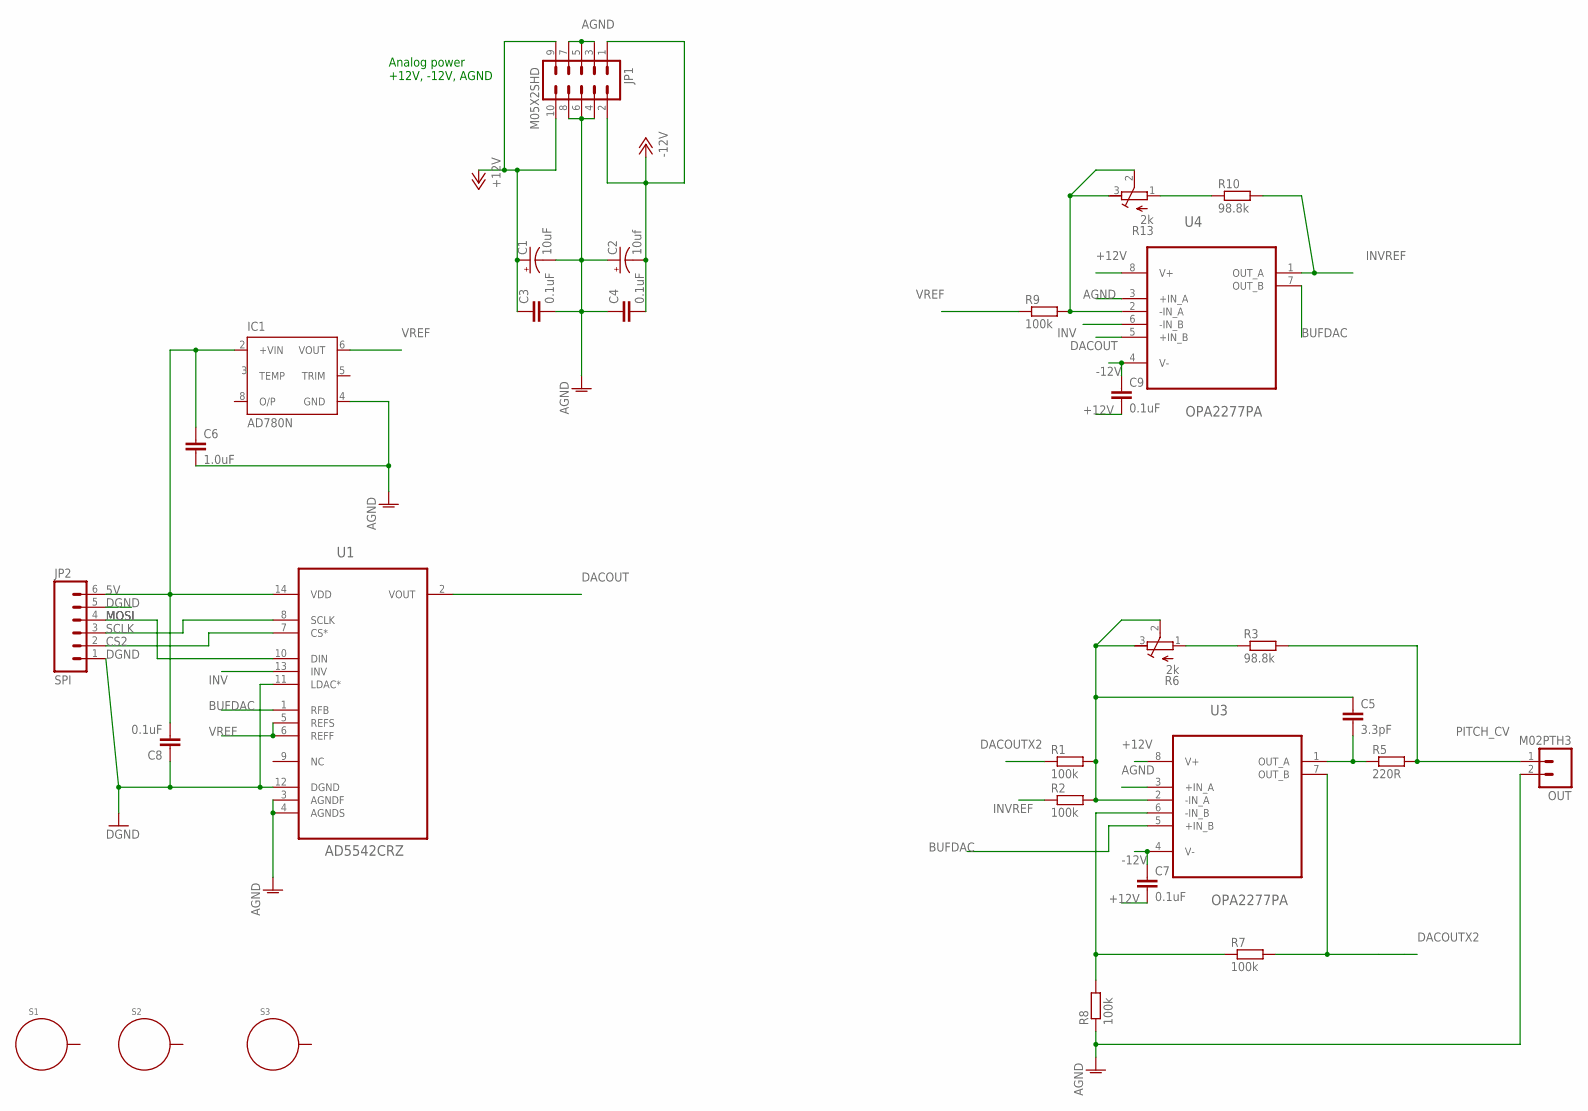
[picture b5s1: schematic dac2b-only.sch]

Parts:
C1: 10uF; CPOL-RADIAL-100UF-25V
C2: 10uf; CPOL-RADIAL-100UF-25V
C3, C4, C8: 0.1uF; C050-055X075
C5: 3.3pF; C025-025X050
C6: 1.0uF; C075-032X103
C7, C9: 0.1uF; C025-025X050
IC1: AD780N; DIL08
JP1: M05X2SHD; 2X5-SHROUDED
JP2: SPI; 1X06
OUT: M02PTH3; 1X02_LONGPADS
R1, R2, R7, R8, R9: 100k; 0207/10
R3, R10: 98.8k; 0207/10
R5: 220R; 0207/10
R6, R13: 2k; RTRIM3296W
S1, S2, S3: STANDOFF_ELECTRICAL; STANDOFF-ELECTRICAL
U1: AD5542CRZ; SOIC127P600X175-14N
U3, U4: OPA2277PA; DIP254P762X508-8

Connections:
5V: C6.1, C8.2, IC1.2 (+VIN), JP2.6, U1.14 (VDD)
+12V: C1.1 (+), C3.1, C7.2, C9.2, JP1.9, JP1.10, U3.8 (V+), U4.8 (V+)
-12V: C2.2 (-), C4.2, C7.1, C9.1, JP1.1, JP1.2, U3.4 (V-), U4.4 (V-)
AGND: C1.2 (-), C2.1 (+), C3.2, C4.1, C6.2, IC1.4 (GND), JP1.3, JP1.4, JP1.5, JP1.6, JP1.7, JP1.8, OUT.2, R8.1, U1.3 (AGNDF), U1.4 (AGNDS), U3.3 (+IN_A), U4.3 (+IN_A)
BUFDAC: U1.1 (RFB), U3.5 (+IN_B), U4.7 (OUT_B)
CS2: JP2.2, U1.7 (CS*)
DACOUT: U1.2 (VOUT), U4.5 (+IN_B)
DACOUTX2: R1.1, R7.2, U3.7 (OUT_B)
DGND: C8.1, JP2.1, JP2.5, U1.11 (LDAC*), U1.12 (DGND)
INV: U1.13 (INV), U4.6 (-IN_B)
INVREF: R2.1, R10.2, U4.1 (OUT_A)
MOSI: JP2.4, U1.10 (DIN)
unnamed: R9.2, R13.2 (S), R13.3 (A), U4.2 (-IN_A)
unnamed: C5.2, R5.1, U3.1 (OUT_A)
unnamed: R10.1, R13.1 (E)
unnamed: C5.1, R1.2, R2.2, R6.2 (S), R6.3 (A), U3.2 (-IN_A)
unnamed: R7.1, R8.2, U3.6 (-IN_B)
unnamed: R3.1, R6.1 (E)
PITCH_CV: OUT.1, R3.2, R5.2
SCLK: JP2.3, U1.8 (SCLK)
VREF: IC1.6 (VOUT), R9.1, U1.5 (REFS), U1.6 (REFF)

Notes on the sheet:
Analog power +12V, -12V, AGND

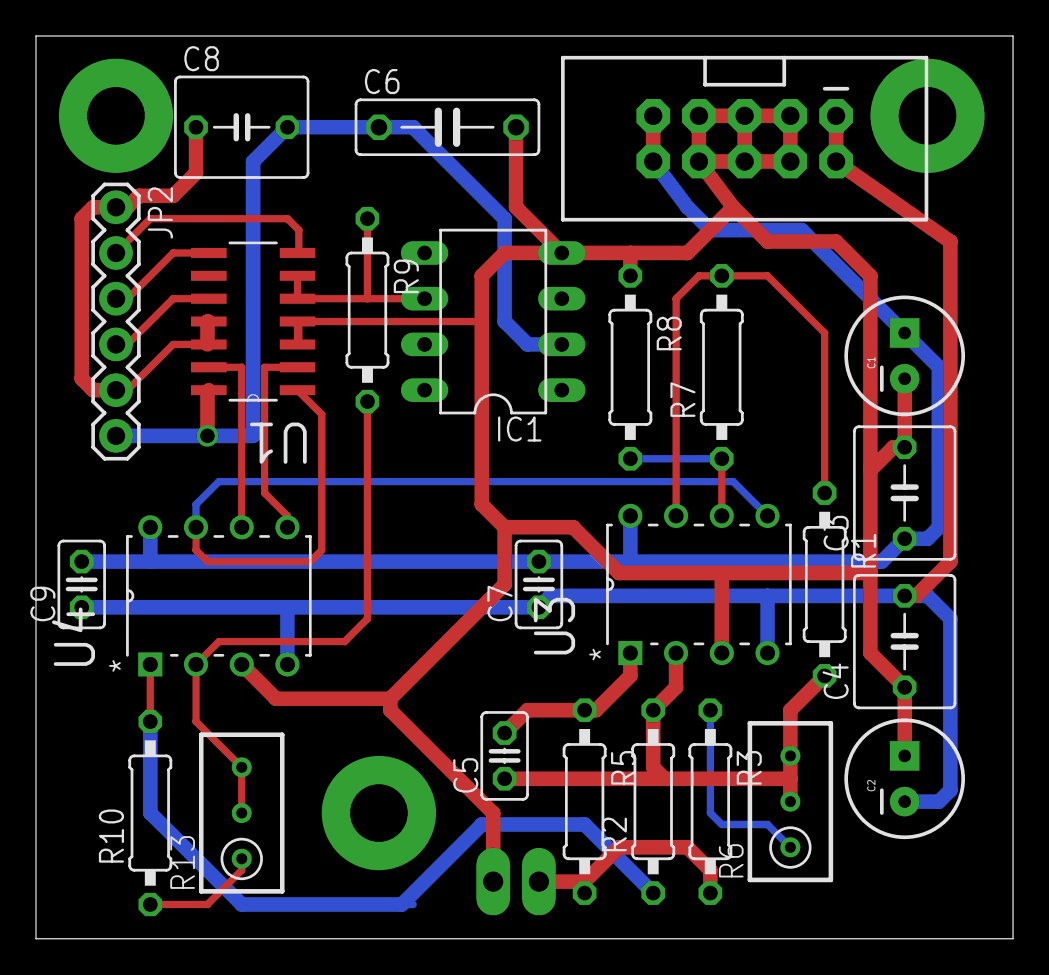
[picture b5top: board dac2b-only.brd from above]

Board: 2 copper layers, 54.3 x 50.2 mm, 29 parts (0 on the bottom side), 21 nets.

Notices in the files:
parts and their libraries:
SparkFun-Connectors: Licensing: Creative Commons ShareAlike 4.0 International - https://creativecommons.org/licenses/by-sa/4.0
SparkFun-Passives: Licensing: CC v3.0 Share-Alike You are welcome to use this library for commercial purposes.
